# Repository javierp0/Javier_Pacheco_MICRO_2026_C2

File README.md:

# Javier_Pacheco_MICRO_2026_C2
Microcontroladores

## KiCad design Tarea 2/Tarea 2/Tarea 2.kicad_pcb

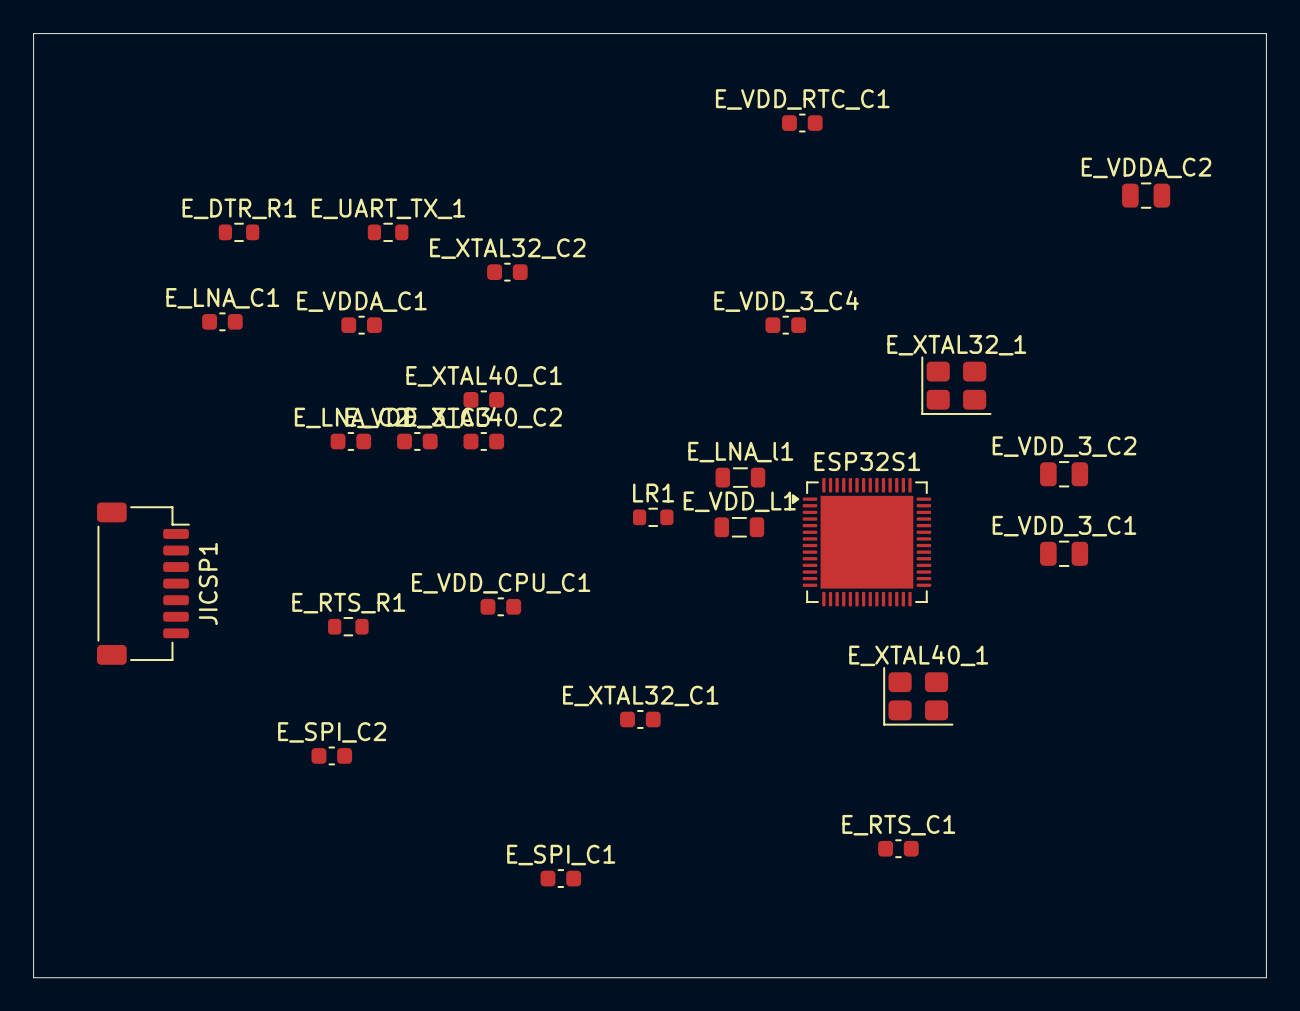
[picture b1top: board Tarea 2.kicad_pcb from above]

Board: 4 copper layers, 74.4 x 57.0 mm, 27 parts (0 on the bottom side), 17 nets, no tracks yet.

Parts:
ESP32S1: ESP32-S3; QFN-56-1EP_7x7mm_P0.4mm_EP5.6x5.6mm
E_DTR_R1: 10k; R_0603_1608Metric
E_LNA_C1, E_LNA_C2: 2.7pF; C_0603_1608Metric
E_LNA_l1: 1.8nH 5%; L_0805_2012Metric
E_RTS_C1: 100nF; C_0603_1608Metric
E_RTS_R1: 10k; R_0603_1608Metric
E_SPI_C1: 1uF 10% 50V; C_0603_1608Metric
E_SPI_C2: 100nF 10% 16V; C_0603_1608Metric
E_UART_TX_1: 499R; R_0603_1608Metric
E_VDDA_C1: 100nF; C_0603_1608Metric
E_VDDA_C2: 1uF 10% 50V; C_0805_2012Metric
E_VDD_3_C1, E_VDD_3_C2: 10uF 20% 6.3V; C_0805_2012Metric
E_VDD_3_C3, E_VDD_3_C4: 100nF 10% 16V; C_0603_1608Metric
E_VDD_CPU_C1: 100nF 10% 16V; C_0603_1608Metric
E_VDD_L1: 12nH 5%; L_0805_2012Metric
E_VDD_RTC_C1: 100nF 10% 16V; C_0603_1608Metric
E_XTAL32_1: 32.768Mhz 22pF+-10PPM; Crystal_SMD_3225-4Pin_3.2x2.5mm
E_XTAL32_C1, E_XTAL32_C2, E_XTAL40_C1, E_XTAL40_C2: 22pF 5% 50V; C_0603_1608Metric
E_XTAL40_1: 40Mhz 22pF+-10PPM; Crystal_SMD_3225-4Pin_3.2x2.5mm
JICSP1: Conn_01x07_Socket; JST_SH_SM07B-SRSS-TB_1x07-1MP_P1.00mm_Horizontal
LR1: 330R; R_0603_1608Metric

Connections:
3V3: ESP32S1.20 (VDD3P3_RTC), ESP32S1.46 (VDD3P3_CPU), ESP32S1.55 (VDDA), ESP32S1.56 (VDDA), E_DTR_R1.1, E_RTS_R1.1, E_VDDA_C1.2, E_VDDA_C2.2, E_VDD_3_C1.1, E_VDD_3_C2.1, E_VDD_3_C3.1, E_VDD_CPU_C1.1, E_VDD_L1.1, E_VDD_RTC_C1.1, JICSP1.1
CHIP_EN: ESP32S1.4 (CHIP_PU/RESET), E_RTS_C1.2, E_RTS_R1.2, JICSP1.7
DAC_CALIBRATION: ESP32S1.19 (GPIO14/ADC2_CH3), ESP32S1.24 (GPIO18/ADC2_CH7/DAC_1)
ESP_GPIO0_BOOT-DTR: ESP32S1.5 (GPIO0/BOOT), ESP32S1.52 (GPIO46), E_DTR_R1.2, JICSP1.6
GND: ESP32S1.8 (GPIO3/ADC1_CH2), ESP32S1.51 (GPIO45), ESP32S1.57 (GND), E_LNA_C1.2, E_LNA_C2.2, E_RTS_C1.1, E_SPI_C1.2, E_SPI_C2.2, E_VDDA_C1.1, E_VDDA_C2.1, E_VDD_3_C1.2, E_VDD_3_C2.2, E_VDD_3_C3.2, E_VDD_3_C4.2, E_VDD_CPU_C1.2, E_VDD_RTC_C1.2, E_XTAL32_1.2, E_XTAL32_1.4, E_XTAL32_C1.2, E_XTAL32_C2.2, E_XTAL40_1.2, E_XTAL40_1.4, E_XTAL40_C1.2, E_XTAL40_C2.2, JICSP1.2
LED_R_IO04: ESP32S1.9 (GPIO4/ADC1_CH3), LR1.1
unnamed: ESP32S1.21 (GPIO15/ADC2_CH4/XTAL_32K_P), E_XTAL32_1.3, E_XTAL32_C1.1
unnamed: ESP32S1.22 (GPIO16/ADC2_CH5/XTAL_32K_N), E_XTAL32_1.1, E_XTAL32_C2.1
unnamed: ESP32S1.1 (LNA_IN/RF), E_LNA_C2.1, E_LNA_l1.2
unnamed: ESP32S1.49 (U0TXD/PROG/GPIO43), E_UART_TX_1.2
unnamed: ESP32S1.2 (VDD3P3), ESP32S1.3 (VDD3P3), E_VDD_3_C4.1, E_VDD_L1.2
unnamed: ESP32S1.53 (XTAL_N), E_XTAL40_1.3, E_XTAL40_C2.1
unnamed: ESP32S1.54 (XTAL_P), E_XTAL40_1.1, E_XTAL40_C1.1
unnamed: E_LNA_C1.1, E_LNA_l1.1
RXD0: ESP32S1.50 (U0RXD/PROG/GPIO44), JICSP1.5
TXD0: E_UART_TX_1.1, JICSP1.4
VDD_SPI: ESP32S1.29 (VDD_SPI), E_SPI_C1.1, E_SPI_C2.1
